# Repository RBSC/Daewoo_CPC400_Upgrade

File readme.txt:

-------------------------------------------------
Daewoo CPC-400/400S MSX2/MSX2+ Conversion Project
Created and Published by RBSC in 2026
Special thanks to Max Vlasov [Meteor-M]
-------------------------------------------------

The documentation for the project can be found in the DOCs folder of this repository. It consists of two PDF files. One file contains
information about the history of the project and how it was created, the second file contains instructions on how to make necessary
modifications to the hardware and what files to burn/flash into EPROM/GAL chips.

DISCLAIMER
----------

THIS INFORMATION AND RELATED FILES ARE PROVIDED AS IS AND ANY EXPRESS OR IMPLIED WARRANTIES, INCLUDING,BUT NOT LIMITED TO, THE IMPLIED
WARRANTIES OF MERCHANTABILITY AND FITNESS FOR A PARTICULAR PURPOSE ARE DISCLAIMED. IN NO EVENT SHALL THE COPYRIGHT OWNER OR CONTRIBUTORS
BE LIABLE FOR ANY DIRECT, INDIRECT, INCIDENTAL, SPECIAL, EXEMPLARY, OR CONSEQUENTIAL DAMAGES (INCLUDING, BUT NOT LIMITED TO, PROCUREMENT
OF SUBSTITUTE GOODS OR SERVICES; LOSS OF USE, DATA, OR PROFITS; OR BUSINESS INTERRUPTION) HOWEVER CAUSED AND ON ANY THEORY OF LIABILITY,
WHETHER IN CONTRACT, STRICT LIABILITY, OR TORT (INCLUDING NEGLIGENCE OR OTHERWISE) ARISING IN ANY WAY OUT OF THE USE OF THIS SOFTWARE,
EVEN IF ADVISED OF THE POSSIBILITY OF SUCH DAMAGE.

Contact information
-------------------

The members of RBSC group Tnt23, Wierzbowsky, Pyhesty, Ptero, GreyWolf, SuperMax, VWarlock, ALSP and DJS3000 can be contacted via the
group's e-mail address:
info@rbsc.su

The group's coordinator could be reached via this e-mail address:
admin@rbsc.su

The group's website can be found here:
https://rbsc.su/
https://rbsc.su/ru

The RBSC's hardware repository can be found here:
https://github.com/rbsc

The RBSC's 3D model repository can be found here:
https://www.thingiverse.com/groups/rbsc/things

-= ! MSX FOREVER ! =-

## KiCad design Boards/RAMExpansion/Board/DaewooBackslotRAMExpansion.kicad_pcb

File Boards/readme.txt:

-------------------------------------------------
Daewoo CPC-400/400S MSX2/MSX2+ Conversion Project
Created and Published by RBSC in 2026
Special thanks to Max Vlasov [Meteor-M]
-------------------------------------------------

These folders contain Gerber files, KiCAD source files. ROMs, BOMs, 3D case files and firmwares for the following boards:

FMPAC Light board (with stereo output)
Slot Expander Board
EPROM/SLOT Daughterboard
RAM Expansion Board
Older RAM Expansion Board (!different firmware for the Slot Expander is required!)

The boards and firmwares were created by Wierzbowsky [RBSC] and Max Vlasov [Meteor-M].

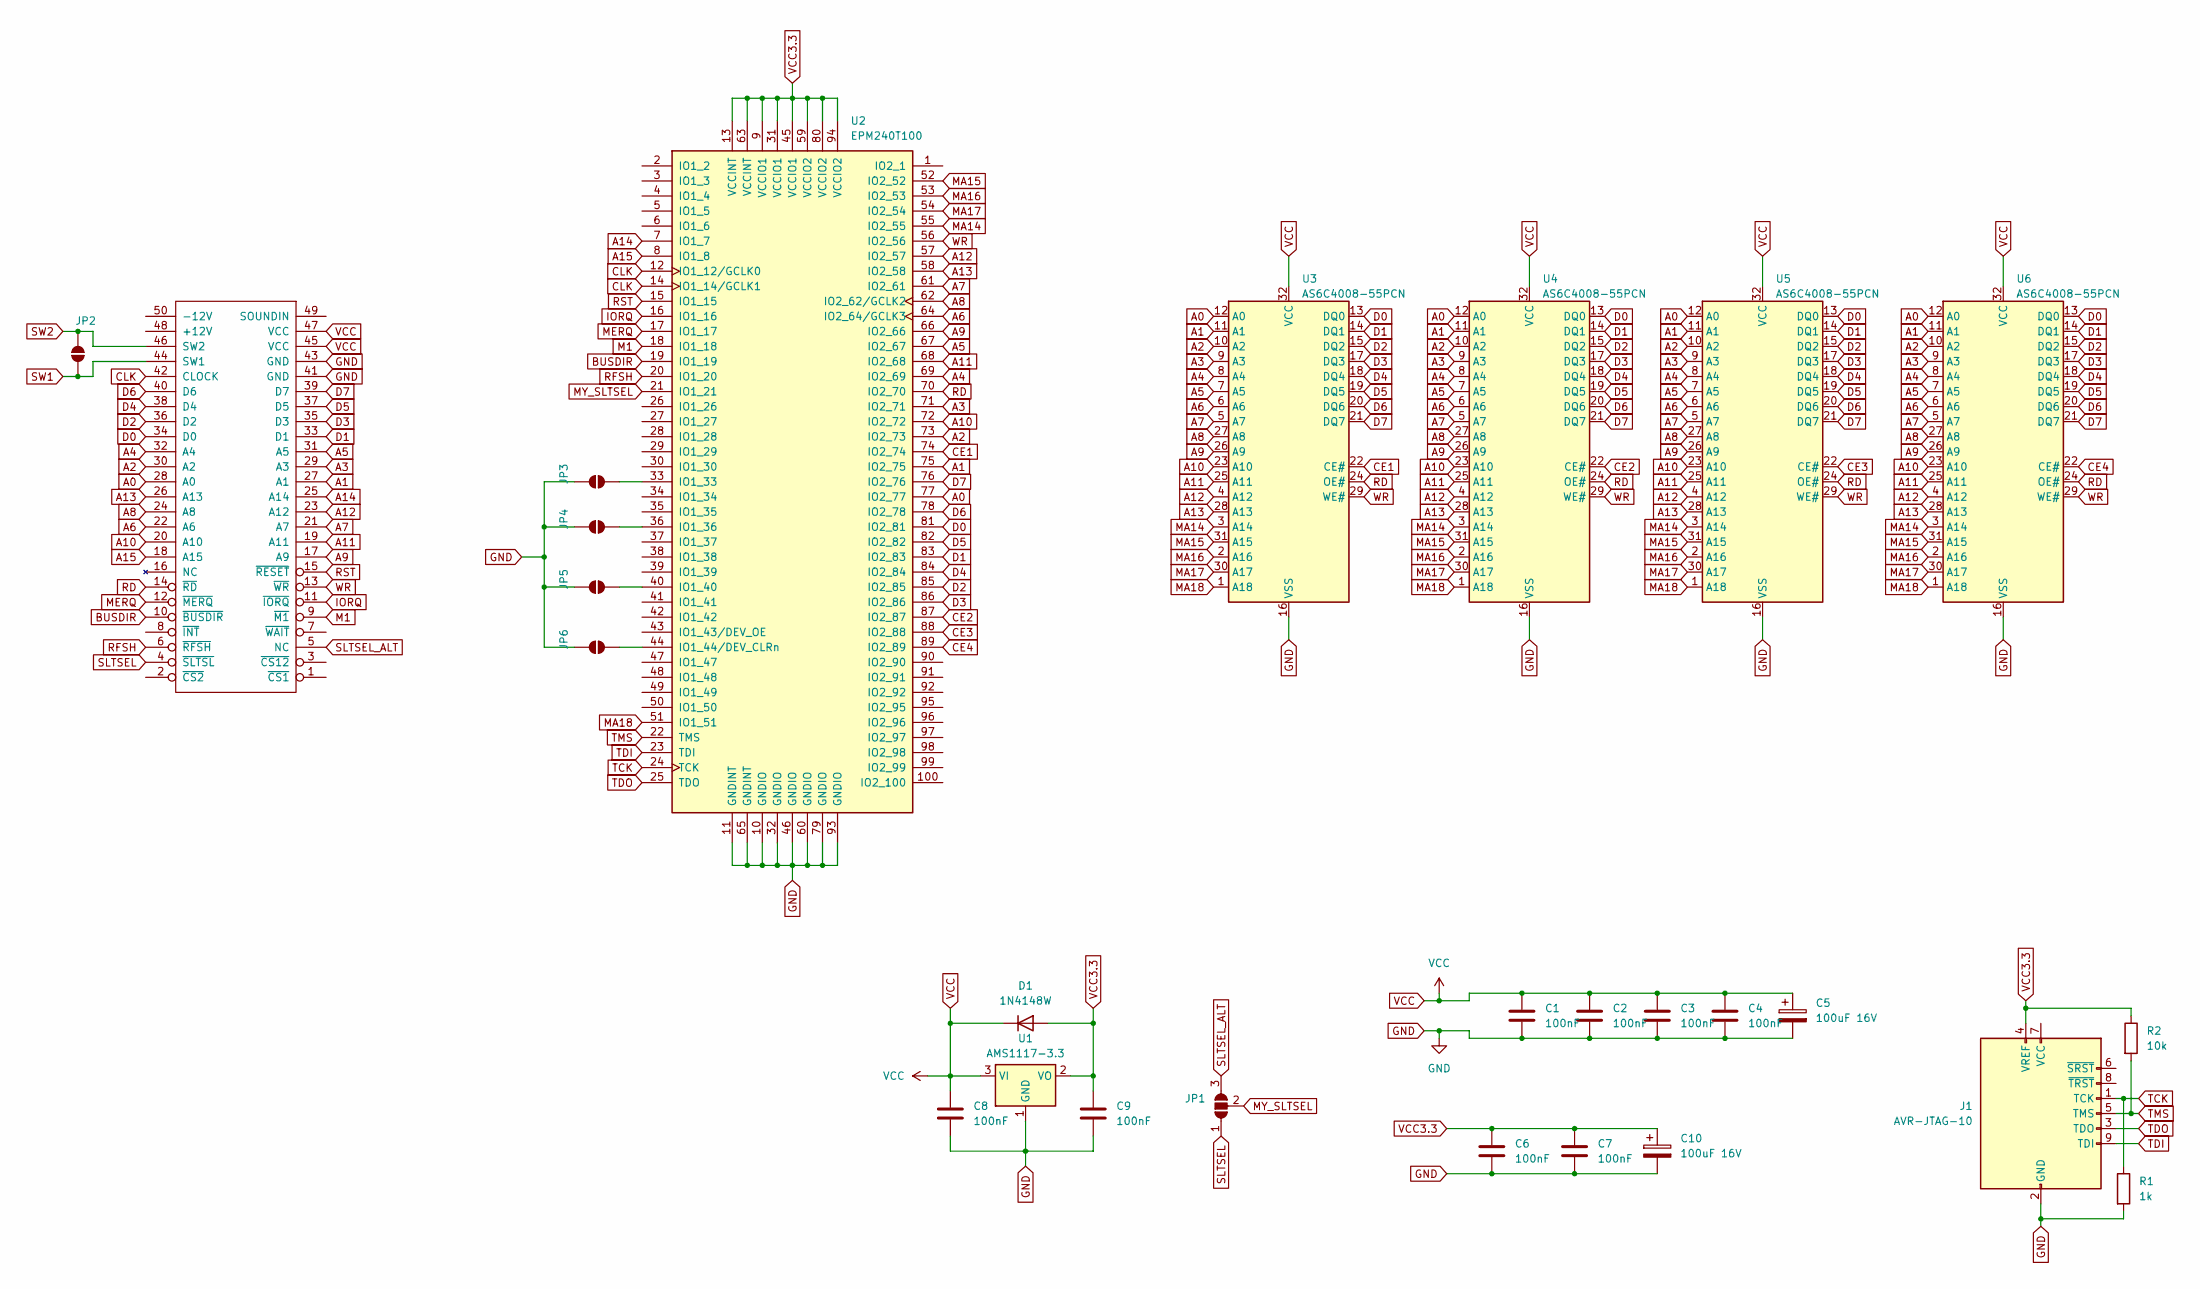
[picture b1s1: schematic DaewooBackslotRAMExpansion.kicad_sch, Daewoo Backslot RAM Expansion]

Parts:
BUS1: my_components_MSX_SLOT_HOST; DaewooBackSlotConnector
C1, C2, C3, C4, C6, C7, C8, C9: 100nF; C_0805_2012Metric
C5, C10: 100uF 16V; CP_Radial_D5.0mm_P2.00mm
D1: 1N4148W; D_SOD-123
J1: AVR-JTAG-10; IDC-Header_2x05_P2.54mm_Vertical
JP1: SolderJumper_3_Open; SolderJumper-3_P1.3mm_Open_RoundedPad1.0x1.5mm_NumberLabels
JP2, JP3, JP4, JP5, JP6: SolderJumper_2_Open; SolderJumper-2_P1.3mm_Open_RoundedPad1.0x1.5mm
R1: 1k; R_0805_2012Metric
R2: 10k; R_0805_2012Metric
U1: AMS1117-3.3; SOT-223-3_TabPin2
U2: EPM240T100; LQFP-100_14x14mm_P0.5mm
U3, U4, U5, U6: AS6C4008-55PCN; SOP-32_11.305x20.495mm_P1.27mm

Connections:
A0: BUS1.28 (A0), U2.77 (IO2_77), U3.12 (A0), U4.12 (A0), U5.12 (A0), U6.12 (A0)
A1: BUS1.27 (A1), U2.75 (IO2_75), U3.11 (A1), U4.11 (A1), U5.11 (A1), U6.11 (A1)
A2: BUS1.30 (A2), U2.73 (IO2_73), U3.10 (A2), U4.10 (A2), U5.10 (A2), U6.10 (A2)
A3: BUS1.29 (A3), U2.71 (IO2_71), U3.9 (A3), U4.9 (A3), U5.9 (A3), U6.9 (A3)
A4: BUS1.32 (A4), U2.69 (IO2_69), U3.8 (A4), U4.8 (A4), U5.8 (A4), U6.8 (A4)
A5: BUS1.31 (A5), U2.67 (IO2_67), U3.7 (A5), U4.7 (A5), U5.7 (A5), U6.7 (A5)
A6: BUS1.22 (A6), U2.64 (IO2_64/GCLK3), U3.6 (A6), U4.6 (A6), U5.6 (A6), U6.6 (A6)
A7: BUS1.21 (A7), U2.61 (IO2_61), U3.5 (A7), U4.5 (A7), U5.5 (A7), U6.5 (A7)
A8: BUS1.24 (A8), U2.62 (IO2_62/GCLK2), U3.27 (A8), U4.27 (A8), U5.27 (A8), U6.27 (A8)
A9: BUS1.17 (A9), U2.66 (IO2_66), U3.26 (A9), U4.26 (A9), U5.26 (A9), U6.26 (A9)
A10: BUS1.20 (A10), U2.72 (IO2_72), U3.23 (A10), U4.23 (A10), U5.23 (A10), U6.23 (A10)
A11: BUS1.19 (A11), U2.68 (IO2_68), U3.25 (A11), U4.25 (A11), U5.25 (A11), U6.25 (A11)
A12: BUS1.23 (A12), U2.57 (IO2_57), U3.4 (A12), U4.4 (A12), U5.4 (A12), U6.4 (A12)
A13: BUS1.26 (A13), U2.58 (IO2_58), U3.28 (A13), U4.28 (A13), U5.28 (A13), U6.28 (A13)
A14: BUS1.25 (A14), U2.7 (IO1_7)
A15: BUS1.18 (A15), U2.8 (IO1_8)
BUSDIR: BUS1.10 (~BUSDIR), U2.19 (IO1_19)
CE1: U2.74 (IO2_74), U3.22 (CE#)
CE2: U2.87 (IO2_87), U4.22 (CE#)
CE3: U2.88 (IO2_88), U5.22 (CE#)
CE4: U2.89 (IO2_89), U6.22 (CE#)
CLK: BUS1.42 (CLOCK), U2.12 (IO1_12/GCLK0), U2.14 (IO1_14/GCLK1)
D0: BUS1.34 (D0), U2.81 (IO2_81), U3.13 (DQ0), U4.13 (DQ0), U5.13 (DQ0), U6.13 (DQ0)
D1: BUS1.33 (D1), U2.83 (IO2_83), U3.14 (DQ1), U4.14 (DQ1), U5.14 (DQ1), U6.14 (DQ1)
D2: BUS1.36 (D2~), U2.85 (IO2_85), U3.15 (DQ2), U4.15 (DQ2), U5.15 (DQ2), U6.15 (DQ2)
D3: BUS1.35 (D3), U2.86 (IO2_86), U3.17 (DQ3), U4.17 (DQ3), U5.17 (DQ3), U6.17 (DQ3)
D4: BUS1.38 (D4), U2.84 (IO2_84), U3.18 (DQ4), U4.18 (DQ4), U5.18 (DQ4), U6.18 (DQ4)
D5: BUS1.37 (D5), U2.82 (IO2_82), U3.19 (DQ5), U4.19 (DQ5), U5.19 (DQ5), U6.19 (DQ5)
D6: BUS1.40 (D6), U2.78 (IO2_78), U3.20 (DQ6), U4.20 (DQ6), U5.20 (DQ6), U6.20 (DQ6)
D7: BUS1.39 (D7), U2.76 (IO2_76), U3.21 (DQ7), U4.21 (DQ7), U5.21 (DQ7), U6.21 (DQ7)
GND: BUS1.41 (GND), BUS1.43 (GND), C1.2, C2.2, C3.2, C4.2, C5.2, C6.2, C7.2, C8.2, C9.2, C10.2, J1.2 (GND), J1.10 (GND), JP3.2 (B), JP4.2 (B), JP5.2 (B), JP6.2 (B), R1.2, U1.1 (GND), U2.10 (GNDIO), U2.11 (GNDINT), U2.32 (GNDIO), U2.46 (GNDIO), U2.60 (GNDIO), U2.65 (GNDINT), U2.79 (GNDIO), U2.93 (GNDIO), U3.16 (VSS), U4.16 (VSS), U5.16 (VSS), U6.16 (VSS)
IORQ: BUS1.11 (~IORQ), U2.16 (IO1_16)
M1: BUS1.9 (~M1), U2.18 (IO1_18)
MA14: U2.55 (IO2_55), U3.3 (A14), U4.3 (A14), U5.3 (A14), U6.3 (A14)
MA15: U2.52 (IO2_52), U3.31 (A15), U4.31 (A15), U5.31 (A15), U6.31 (A15)
MA16: U2.53 (IO2_53), U3.2 (A16), U4.2 (A16), U5.2 (A16), U6.2 (A16)
MA17: U2.54 (IO2_54), U3.30 (A17), U4.30 (A17), U5.30 (A17), U6.30 (A17)
MA18: U2.51 (IO1_51), U3.1 (A18), U4.1 (A18), U5.1 (A18), U6.1 (A18)
MERQ: BUS1.12 (~MERQ), U2.17 (IO1_17)
MY_SLTSEL: JP1.2 (C), U2.21 (IO1_21)
unnamed: JP3.1 (A), U2.33 (IO1_33)
unnamed: JP4.1 (A), U2.36 (IO1_36)
unnamed: JP5.1 (A), U2.40 (IO1_40)
unnamed: JP6.1 (A), U2.44 (IO1_44/DEV_CLRn)
RD: BUS1.14 (~RD), U2.70 (IO2_70), U3.24 (OE#), U4.24 (OE#), U5.24 (OE#), U6.24 (OE#)
RFSH: BUS1.6 (~RFSH), U2.20 (IO1_20)
RST: BUS1.15 (~RESET), U2.15 (IO1_15)
SLTSEL: BUS1.4 (~SLTSL), JP1.1 (A)
SLTSEL_ALT: BUS1.5 (NC), JP1.3 (B)
SW1: BUS1.44 (SW1), JP2.1 (A)
SW2: BUS1.46 (SW2), JP2.2 (B)
TCK: J1.1 (TCK), R1.1, U2.24 (TCK)
TDI: J1.9 (TDI), U2.23 (TDI)
TDO: J1.3 (TDO), U2.25 (TDO)
TMS: J1.5 (TMS), R2.2, U2.22 (TMS)
VCC: BUS1.45 (VCC), BUS1.47 (VCC), C1.1, C2.1, C3.1, C4.1, C5.1, C8.1, D1.1 (K), U1.3 (VI), U3.32 (VCC), U4.32 (VCC), U5.32 (VCC), U6.32 (VCC)
VCC3.3: C6.1, C7.1, C9.1, C10.1, D1.2 (A), J1.4 (VREF), R2.1, U1.2 (VO), U2.9 (VCCIO1), U2.13 (VCCINT), U2.31 (VCCIO1), U2.45 (VCCIO1), U2.59 (VCCIO2), U2.63 (VCCINT), U2.80 (VCCIO2), U2.94 (VCCIO2)
WR: BUS1.13 (~WR), U2.56 (IO2_56), U3.29 (WE#), U4.29 (WE#), U5.29 (WE#), U6.29 (WE#)

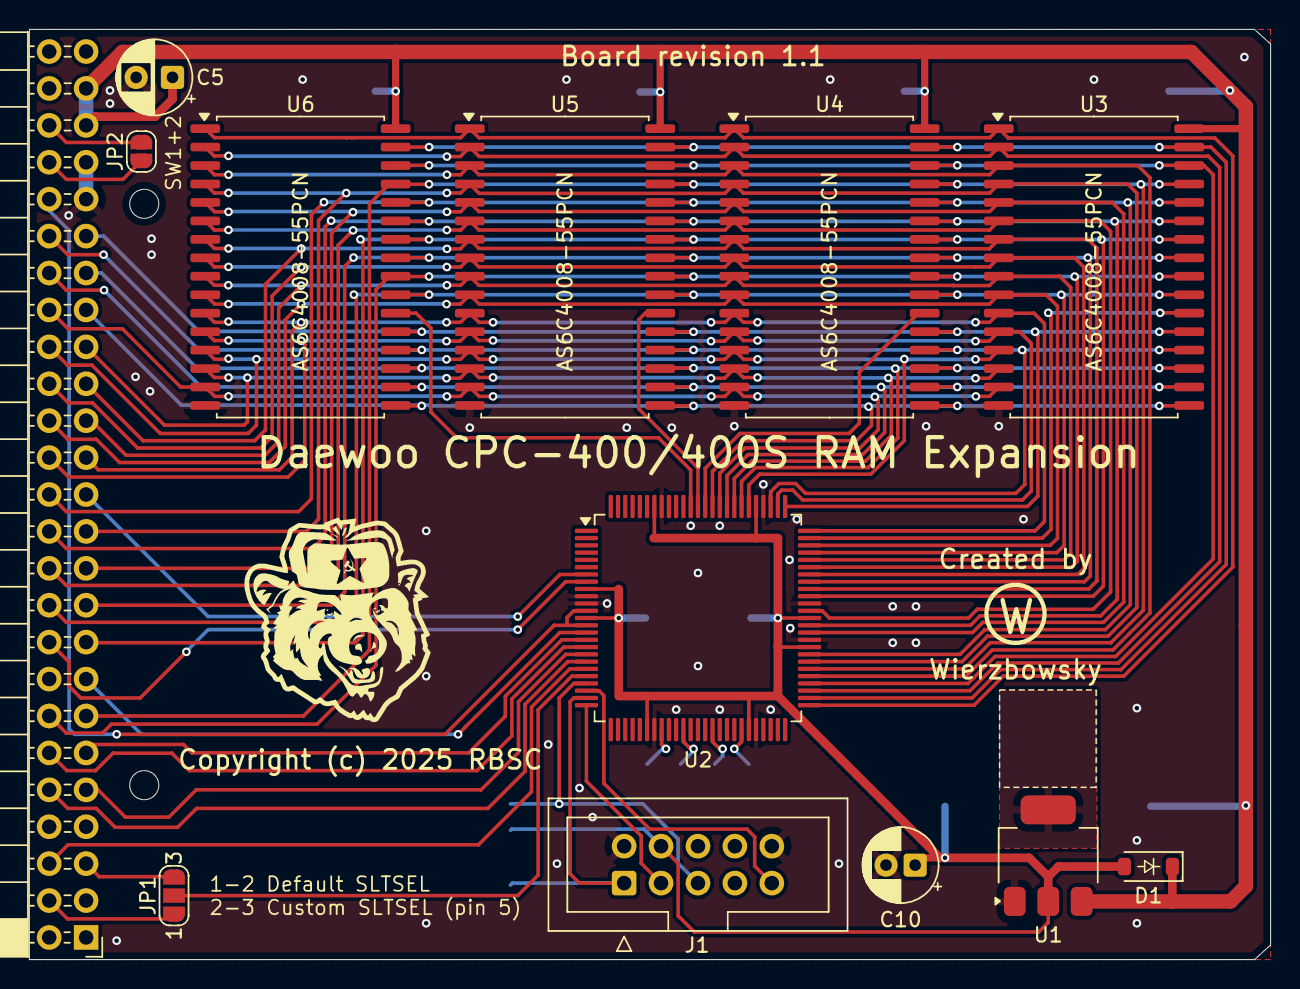
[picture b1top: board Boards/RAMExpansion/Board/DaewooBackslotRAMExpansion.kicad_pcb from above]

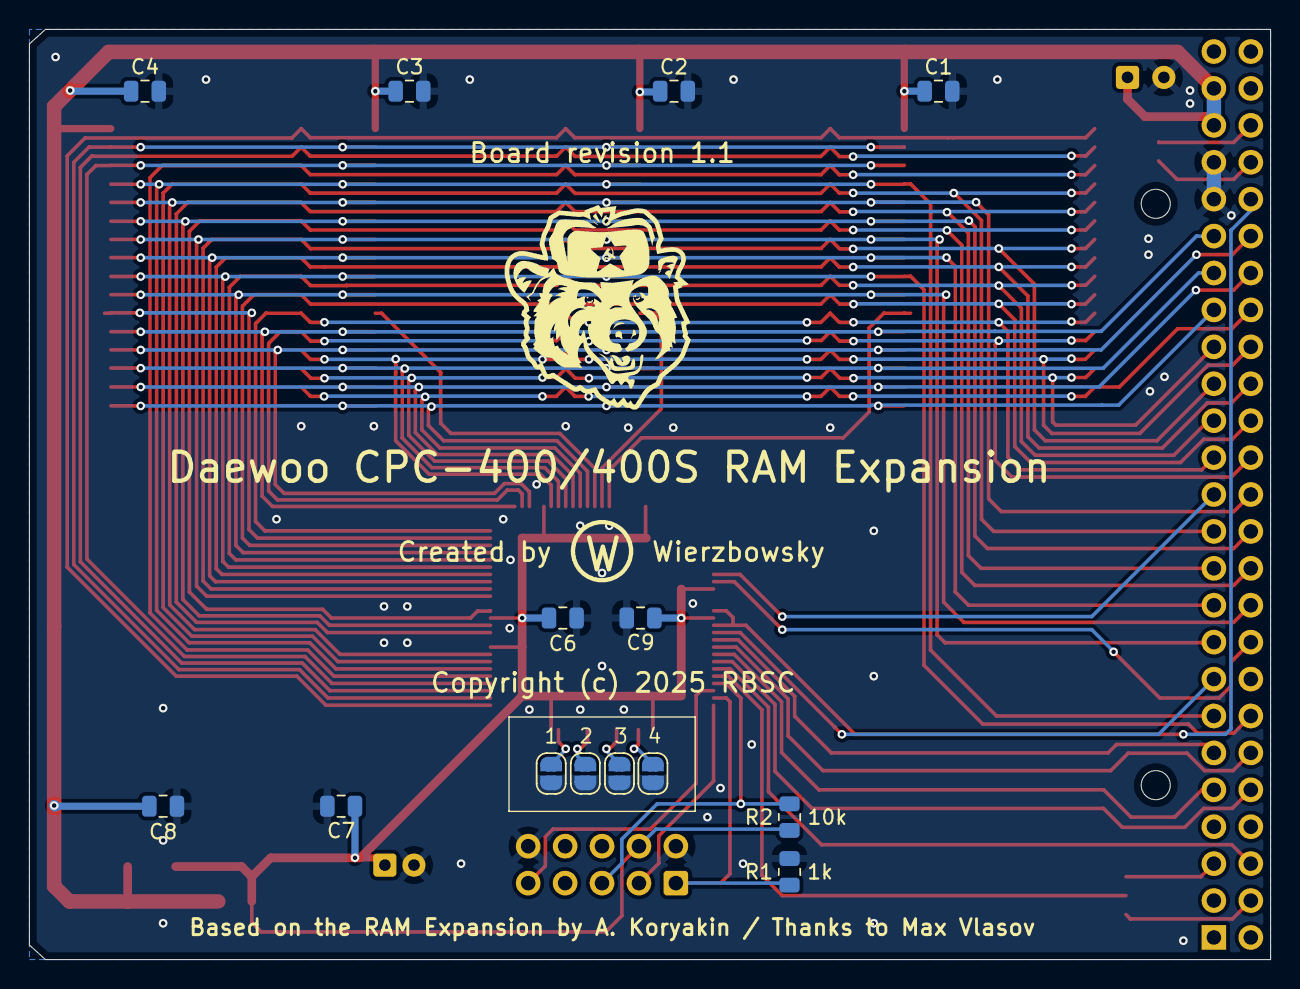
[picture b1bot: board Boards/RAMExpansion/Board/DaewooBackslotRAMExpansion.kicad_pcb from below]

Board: 2 copper layers, 85.4 x 64.0 mm, 27 parts (14 on the bottom side), 58 nets.

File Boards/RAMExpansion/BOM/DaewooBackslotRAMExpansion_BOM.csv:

"Id";"Designator";"Footprint";"Quantity";"Designation";"Supplier and ref";
1;"C5";"CP_Radial_D5.0mm_P2.50mm";1;"100uF 16V";;;
2;"D1";"D_SOD-123";1;"1N4148W";;;
3;"U5,U4,U3,U6";"SOP-32_11.305x20.495mm_P1.27mm";4;"AS6C4008-55PCN";;;
4;"U2";"LQFP-100_14x14mm_P0.5mm";1;"EPM240T100";;;
5;"U1";"SOT-223-3_TabPin2";1;"AMS1117-3.3";;;
6;"C10";"CP_Radial_D5.0mm_P2.00mm";1;"100uF 16V";;;
7;"J1";"IDC-Header_2x05_P2.54mm_Vertical";1;"AVR-JTAG-10";;;
8;"BUS1";"DaewooBackSlotConnector";1;"my_components_MSX_SLOT_HOST";;;
9;"C7,C2,C8,C4,C9,C3,C1,C6";"C_0805_2012Metric";8;"100nF";;;
10;"R2";"R_0805_2012Metric";1;"10k";;;
11;"R1";"R_0805_2012Metric";1;"1k";;;

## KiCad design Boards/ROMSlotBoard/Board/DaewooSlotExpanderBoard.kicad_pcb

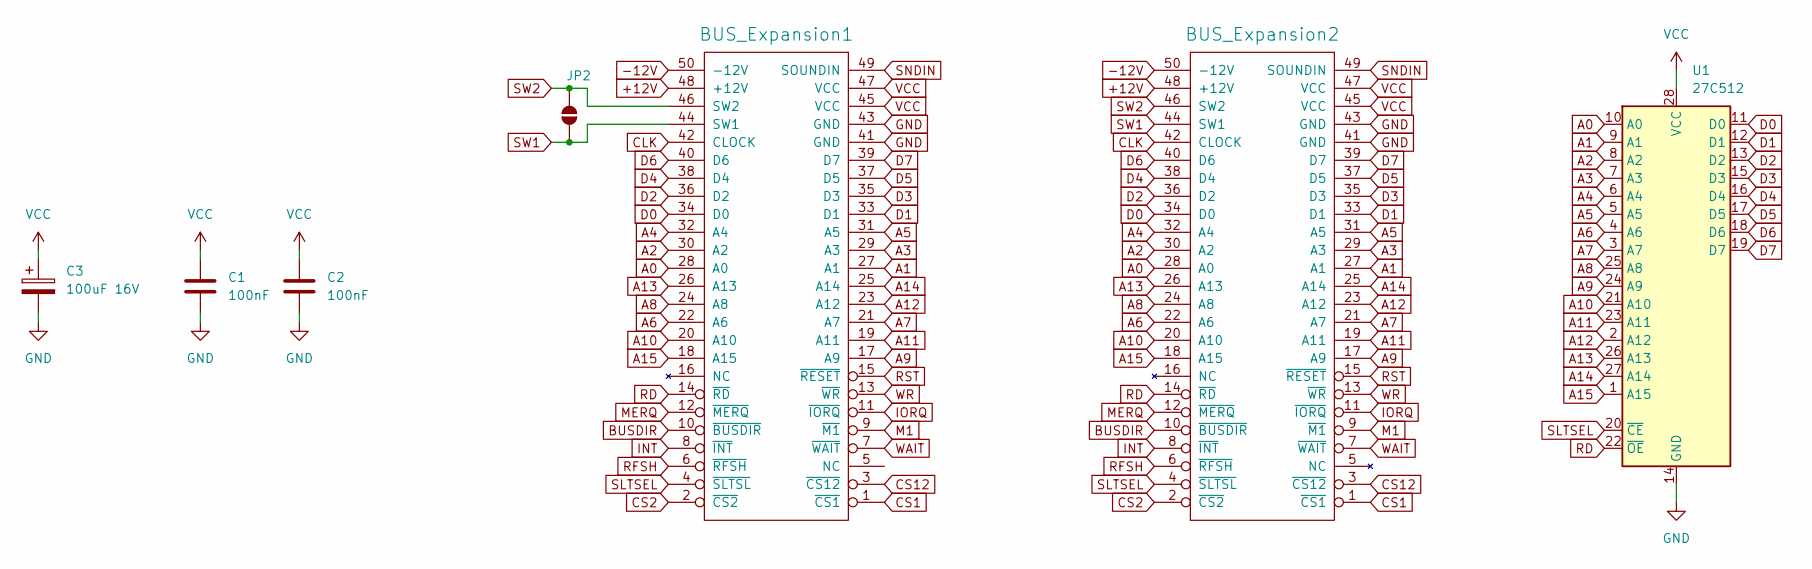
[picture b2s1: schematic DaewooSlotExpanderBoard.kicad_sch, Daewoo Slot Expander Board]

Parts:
BUS_Expansion1: my_components_MSX_SLOT_HOST; DaewooBackSlotConnector
BUS_Expansion2: my_components_MSX_SLOT_HOST; PinHeader_2x25_P2.54mm_Vertical
C1, C2: 100nF; C_0805_2012Metric
C3: 100uF 16V; CP_Radial_D5.0mm_P2.00mm
JP2: SolderJumper_2_Open; SolderJumper-2_P1.3mm_Open_RoundedPad1.0x1.5mm
U1: 27C512; DIP-28_W15.24mm

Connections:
+12V: BUS_Expansion1.48 (+12V), BUS_Expansion2.48 (+12V)
-12V: BUS_Expansion1.50 (-12V), BUS_Expansion2.50 (-12V)
A0: BUS_Expansion1.28 (A0), BUS_Expansion2.28 (A0), U1.10 (A0)
A1: BUS_Expansion1.27 (A1), BUS_Expansion2.27 (A1), U1.9 (A1)
A2: BUS_Expansion1.30 (A2), BUS_Expansion2.30 (A2), U1.8 (A2)
A3: BUS_Expansion1.29 (A3), BUS_Expansion2.29 (A3), U1.7 (A3)
A4: BUS_Expansion1.32 (A4), BUS_Expansion2.32 (A4), U1.6 (A4)
A5: BUS_Expansion1.31 (A5), BUS_Expansion2.31 (A5), U1.5 (A5)
A6: BUS_Expansion1.22 (A6), BUS_Expansion2.22 (A6), U1.4 (A6)
A7: BUS_Expansion1.21 (A7), BUS_Expansion2.21 (A7), U1.3 (A7)
A8: BUS_Expansion1.24 (A8), BUS_Expansion2.24 (A8), U1.25 (A8)
A9: BUS_Expansion1.17 (A9), BUS_Expansion2.17 (A9), U1.24 (A9)
A10: BUS_Expansion1.20 (A10), BUS_Expansion2.20 (A10), U1.21 (A10)
A11: BUS_Expansion1.19 (A11), BUS_Expansion2.19 (A11), U1.23 (A11)
A12: BUS_Expansion1.23 (A12), BUS_Expansion2.23 (A12), U1.2 (A12)
A13: BUS_Expansion1.26 (A13), BUS_Expansion2.26 (A13), U1.26 (A13)
A14: BUS_Expansion1.25 (A14), BUS_Expansion2.25 (A14), U1.27 (A14)
A15: BUS_Expansion1.18 (A15), BUS_Expansion2.18 (A15), U1.1 (A15)
BUSDIR: BUS_Expansion1.10 (~BUSDIR), BUS_Expansion2.10 (~BUSDIR)
CLK: BUS_Expansion1.42 (CLOCK), BUS_Expansion2.42 (CLOCK)
CS1: BUS_Expansion1.1 (~CS1), BUS_Expansion2.1 (~CS1)
CS2: BUS_Expansion1.2 (~CS2), BUS_Expansion2.2 (~CS2)
CS12: BUS_Expansion1.3 (~CS12), BUS_Expansion2.3 (~CS12)
D0: BUS_Expansion1.34 (D0), BUS_Expansion2.34 (D0), U1.11 (D0)
D1: BUS_Expansion1.33 (D1), BUS_Expansion2.33 (D1), U1.12 (D1)
D2: BUS_Expansion1.36 (D2~), BUS_Expansion2.36 (D2~), U1.13 (D2)
D3: BUS_Expansion1.35 (D3), BUS_Expansion2.35 (D3), U1.15 (D3)
D4: BUS_Expansion1.38 (D4), BUS_Expansion2.38 (D4), U1.16 (D4)
D5: BUS_Expansion1.37 (D5), BUS_Expansion2.37 (D5), U1.17 (D5)
D6: BUS_Expansion1.40 (D6), BUS_Expansion2.40 (D6), U1.18 (D6)
D7: BUS_Expansion1.39 (D7), BUS_Expansion2.39 (D7), U1.19 (D7)
GND: BUS_Expansion1.41 (GND), BUS_Expansion1.43 (GND), BUS_Expansion2.41 (GND), BUS_Expansion2.43 (GND), C1.2, C2.2, C3.2, U1.14 (GND)
INT: BUS_Expansion1.8 (~INT), BUS_Expansion2.8 (~INT)
IORQ: BUS_Expansion1.11 (~IORQ), BUS_Expansion2.11 (~IORQ)
M1: BUS_Expansion1.9 (~M1), BUS_Expansion2.9 (~M1)
MERQ: BUS_Expansion1.12 (~MERQ), BUS_Expansion2.12 (~MERQ)
RD: BUS_Expansion1.14 (~RD), BUS_Expansion2.14 (~RD), U1.22 (~OE)
RFSH: BUS_Expansion1.6 (~RFSH), BUS_Expansion2.6 (~RFSH)
RST: BUS_Expansion1.15 (~RESET), BUS_Expansion2.15 (~RESET)
SLTSEL: BUS_Expansion1.4 (~SLTSL), BUS_Expansion2.4 (~SLTSL), U1.20 (~CE)
SNDIN: BUS_Expansion1.49 (SOUNDIN), BUS_Expansion2.49 (SOUNDIN)
SW1: BUS_Expansion1.44 (SW1), BUS_Expansion2.44 (SW1), JP2.1 (A)
SW2: BUS_Expansion1.46 (SW2), BUS_Expansion2.46 (SW2), JP2.2 (B)
VCC: BUS_Expansion1.45 (VCC), BUS_Expansion1.47 (VCC), BUS_Expansion2.45 (VCC), BUS_Expansion2.47 (VCC), C1.1, C2.1, C3.1, U1.28 (VCC)
WAIT: BUS_Expansion1.7 (~WAIT), BUS_Expansion2.7 (~WAIT)
WR: BUS_Expansion1.13 (~WR), BUS_Expansion2.13 (~WR)

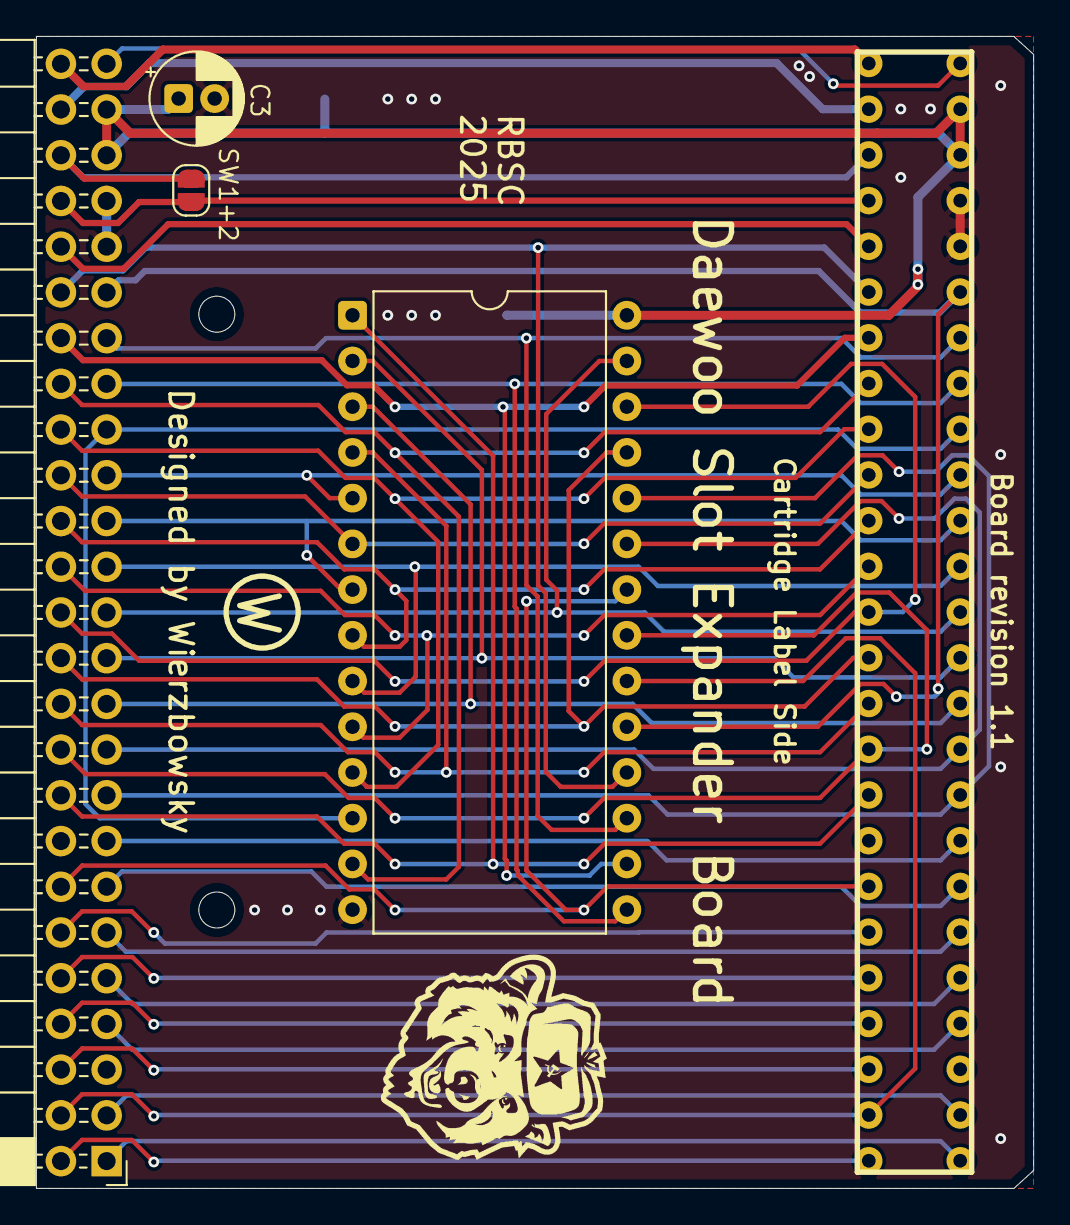
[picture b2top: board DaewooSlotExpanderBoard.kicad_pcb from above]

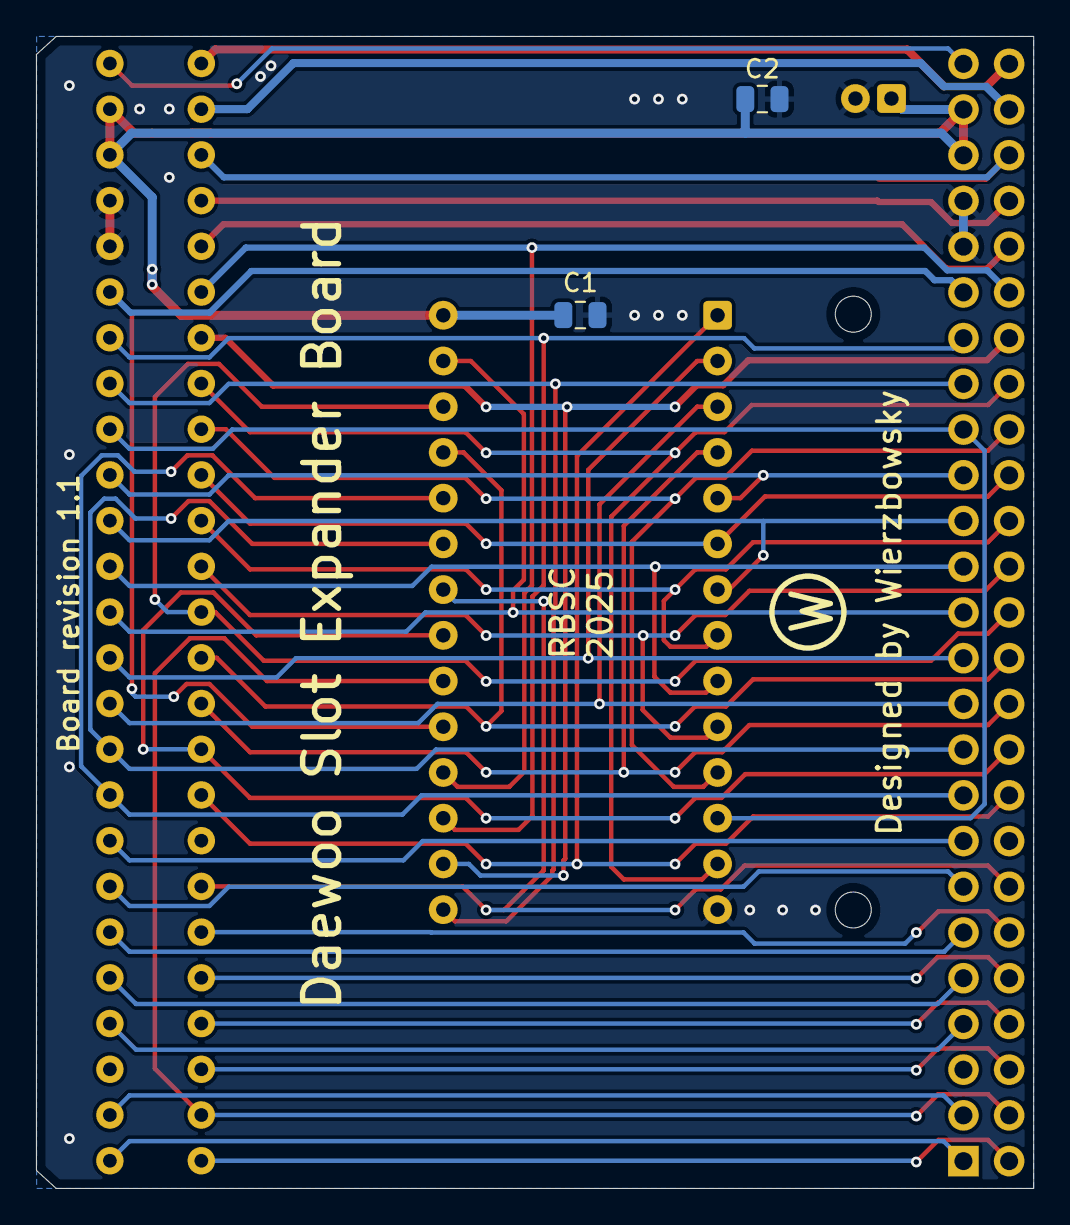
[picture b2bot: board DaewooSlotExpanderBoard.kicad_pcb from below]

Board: 2 copper layers, 55.4 x 64.0 mm, 7 parts (2 on the bottom side), 46 nets.

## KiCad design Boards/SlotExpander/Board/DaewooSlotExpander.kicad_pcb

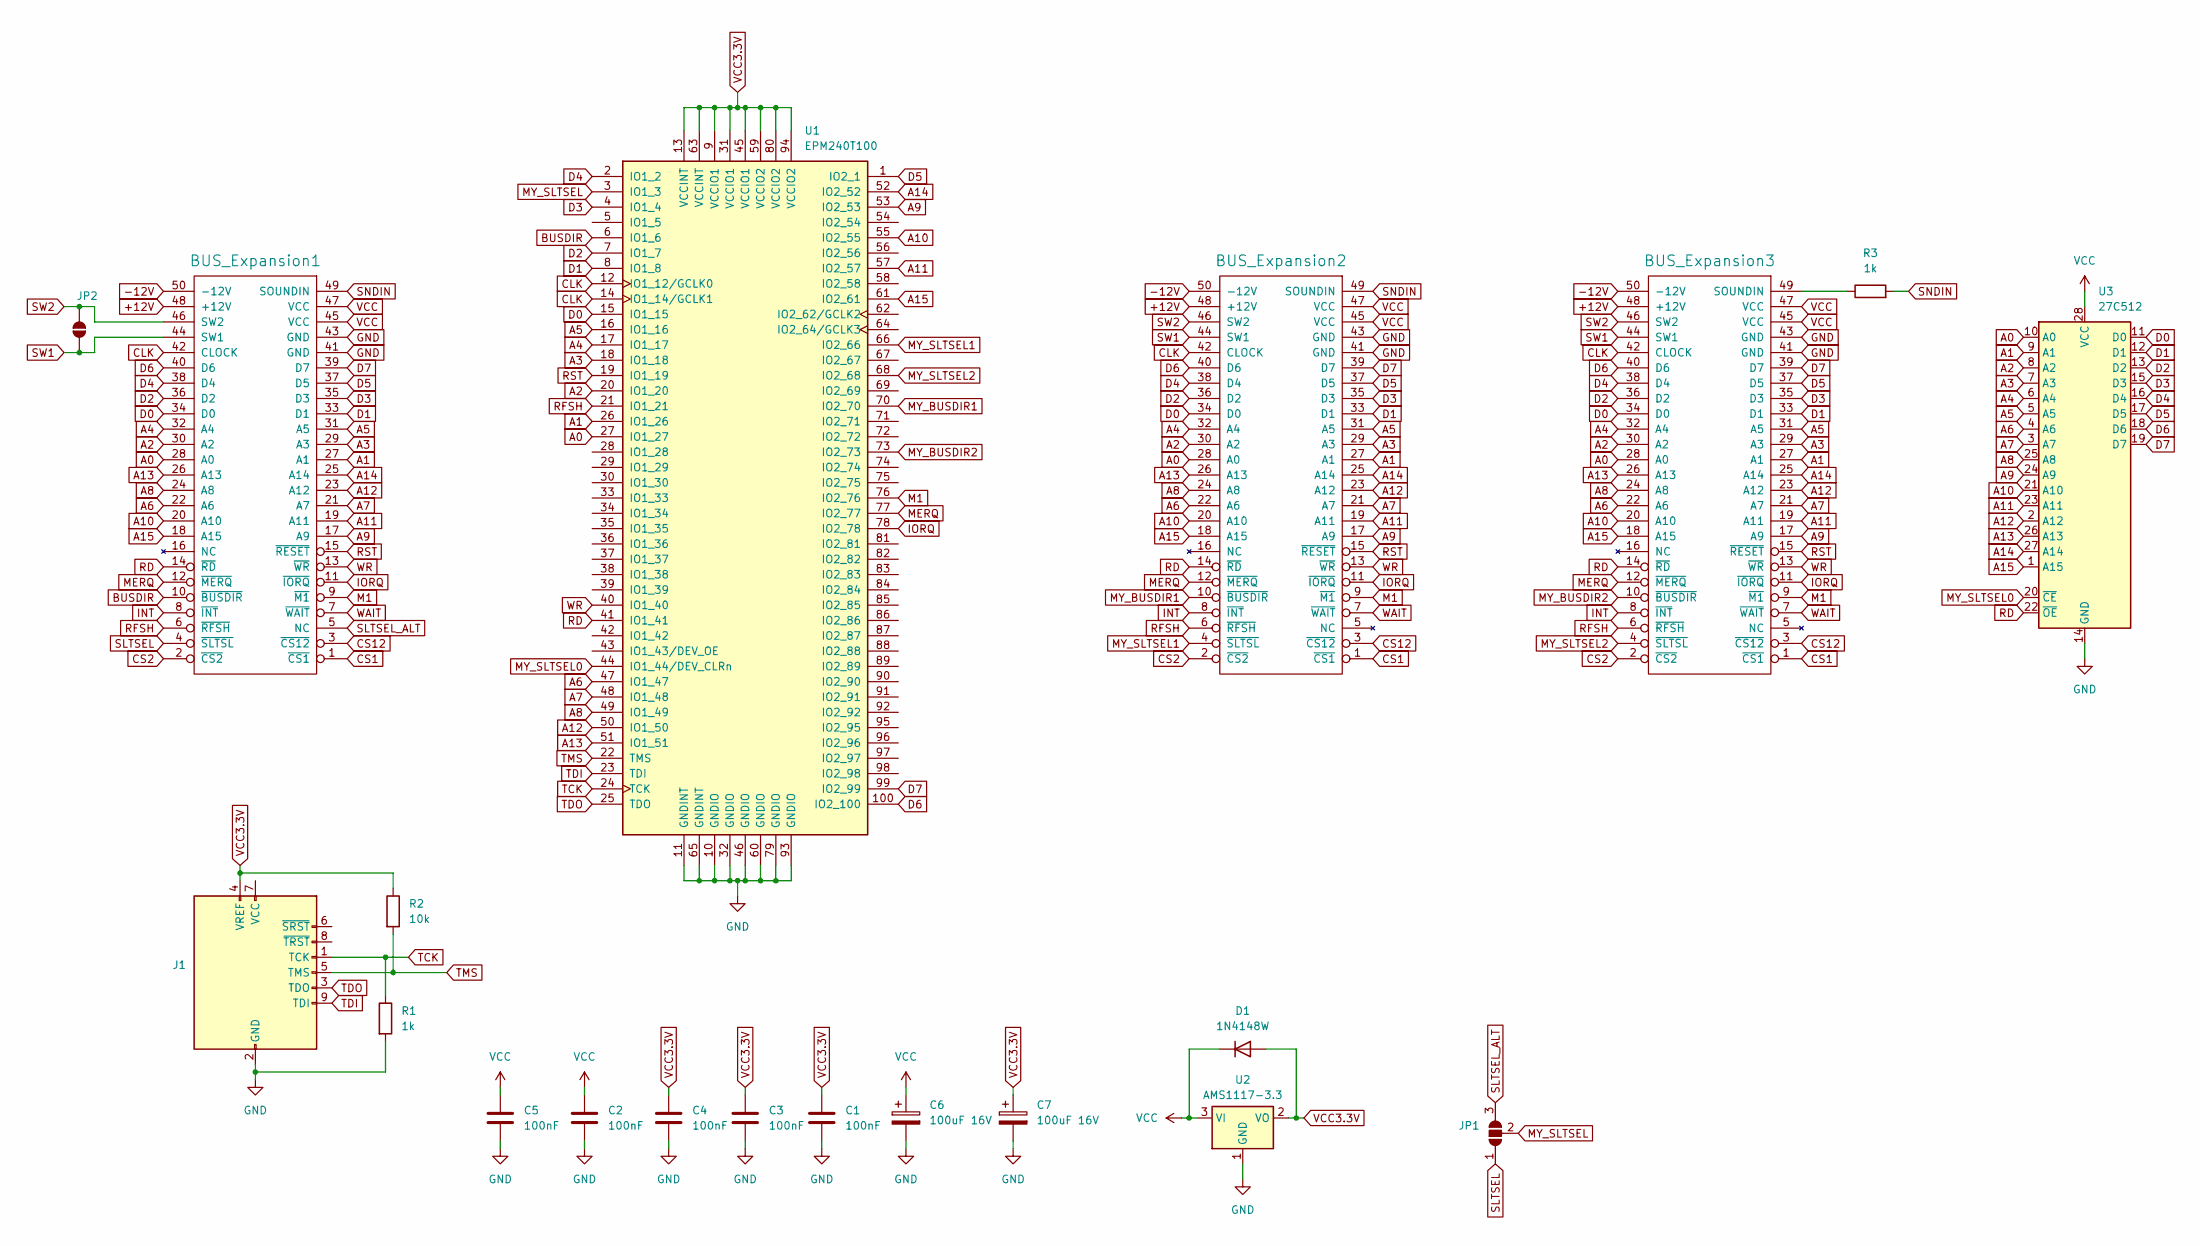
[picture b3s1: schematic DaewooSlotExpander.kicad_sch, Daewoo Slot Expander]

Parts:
BUS_Expansion1: my_components_MSX_SLOT_HOST; DaewooBackSlotConnector
BUS_Expansion2, BUS_Expansion3: my_components_MSX_SLOT_HOST; PinHeader_2x25_P2.54mm_Vertical
C1, C2, C3, C4, C5: 100nF; C_0805_2012Metric
C6, C7: 100uF 16V; CP_Radial_D5.0mm_P2.00mm
D1: 1N4148W; D_SOD-123
J1: AVR-JTAG-10; IDC-Header_2x05_P2.54mm_Vertical
JP1: SolderJumper_3_Open; SolderJumper-3_P1.3mm_Open_RoundedPad1.0x1.5mm_NumberLabels
JP2: SolderJumper_2_Open; SolderJumper-2_P1.3mm_Open_RoundedPad1.0x1.5mm
R1, R3: 1k; R_0805_2012Metric
R2: 10k; R_0805_2012Metric
U1: EPM240T100; LQFP-100_14x14mm_P0.5mm
U2: AMS1117-3.3; SOT-223-3_TabPin2
U3: 27C512; DIP-28_W15.24mm

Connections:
+12V: BUS_Expansion1.48 (+12V), BUS_Expansion2.48 (+12V), BUS_Expansion3.48 (+12V)
-12V: BUS_Expansion1.50 (-12V), BUS_Expansion2.50 (-12V), BUS_Expansion3.50 (-12V)
A0: BUS_Expansion1.28 (A0), BUS_Expansion2.28 (A0), BUS_Expansion3.28 (A0), U1.27 (IO1_27), U3.10 (A0)
A1: BUS_Expansion1.27 (A1), BUS_Expansion2.27 (A1), BUS_Expansion3.27 (A1), U1.26 (IO1_26), U3.9 (A1)
A2: BUS_Expansion1.30 (A2), BUS_Expansion2.30 (A2), BUS_Expansion3.30 (A2), U1.20 (IO1_20), U3.8 (A2)
A3: BUS_Expansion1.29 (A3), BUS_Expansion2.29 (A3), BUS_Expansion3.29 (A3), U1.18 (IO1_18), U3.7 (A3)
A4: BUS_Expansion1.32 (A4), BUS_Expansion2.32 (A4), BUS_Expansion3.32 (A4), U1.17 (IO1_17), U3.6 (A4)
A5: BUS_Expansion1.31 (A5), BUS_Expansion2.31 (A5), BUS_Expansion3.31 (A5), U1.16 (IO1_16), U3.5 (A5)
A6: BUS_Expansion1.22 (A6), BUS_Expansion2.22 (A6), BUS_Expansion3.22 (A6), U1.47 (IO1_47), U3.4 (A6)
A7: BUS_Expansion1.21 (A7), BUS_Expansion2.21 (A7), BUS_Expansion3.21 (A7), U1.48 (IO1_48), U3.3 (A7)
A8: BUS_Expansion1.24 (A8), BUS_Expansion2.24 (A8), BUS_Expansion3.24 (A8), U1.49 (IO1_49), U3.25 (A8)
A9: BUS_Expansion1.17 (A9), BUS_Expansion2.17 (A9), BUS_Expansion3.17 (A9), U1.53 (IO2_53), U3.24 (A9)
A10: BUS_Expansion1.20 (A10), BUS_Expansion2.20 (A10), BUS_Expansion3.20 (A10), U1.55 (IO2_55), U3.21 (A10)
A11: BUS_Expansion1.19 (A11), BUS_Expansion2.19 (A11), BUS_Expansion3.19 (A11), U1.57 (IO2_57), U3.23 (A11)
A12: BUS_Expansion1.23 (A12), BUS_Expansion2.23 (A12), BUS_Expansion3.23 (A12), U1.50 (IO1_50), U3.2 (A12)
A13: BUS_Expansion1.26 (A13), BUS_Expansion2.26 (A13), BUS_Expansion3.26 (A13), U1.51 (IO1_51), U3.26 (A13)
A14: BUS_Expansion1.25 (A14), BUS_Expansion2.25 (A14), BUS_Expansion3.25 (A14), U1.52 (IO2_52), U3.27 (A14)
A15: BUS_Expansion1.18 (A15), BUS_Expansion2.18 (A15), BUS_Expansion3.18 (A15), U1.61 (IO2_61), U3.1 (A15)
BUSDIR: BUS_Expansion1.10 (~BUSDIR), U1.6 (IO1_6)
CLK: BUS_Expansion1.42 (CLOCK), BUS_Expansion2.42 (CLOCK), BUS_Expansion3.42 (CLOCK), U1.12 (IO1_12/GCLK0), U1.14 (IO1_14/GCLK1)
CS1: BUS_Expansion1.1 (~CS1), BUS_Expansion2.1 (~CS1), BUS_Expansion3.1 (~CS1)
CS2: BUS_Expansion1.2 (~CS2), BUS_Expansion2.2 (~CS2), BUS_Expansion3.2 (~CS2)
CS12: BUS_Expansion1.3 (~CS12), BUS_Expansion2.3 (~CS12), BUS_Expansion3.3 (~CS12)
D0: BUS_Expansion1.34 (D0), BUS_Expansion2.34 (D0), BUS_Expansion3.34 (D0), U1.15 (IO1_15), U3.11 (D0)
D1: BUS_Expansion1.33 (D1), BUS_Expansion2.33 (D1), BUS_Expansion3.33 (D1), U1.8 (IO1_8), U3.12 (D1)
D2: BUS_Expansion1.36 (D2~), BUS_Expansion2.36 (D2~), BUS_Expansion3.36 (D2~), U1.7 (IO1_7), U3.13 (D2)
D3: BUS_Expansion1.35 (D3), BUS_Expansion2.35 (D3), BUS_Expansion3.35 (D3), U1.4 (IO1_4), U3.15 (D3)
D4: BUS_Expansion1.38 (D4), BUS_Expansion2.38 (D4), BUS_Expansion3.38 (D4), U1.2 (IO1_2), U3.16 (D4)
D5: BUS_Expansion1.37 (D5), BUS_Expansion2.37 (D5), BUS_Expansion3.37 (D5), U1.1 (IO2_1), U3.17 (D5)
D6: BUS_Expansion1.40 (D6), BUS_Expansion2.40 (D6), BUS_Expansion3.40 (D6), U1.100 (IO2_100), U3.18 (D6)
D7: BUS_Expansion1.39 (D7), BUS_Expansion2.39 (D7), BUS_Expansion3.39 (D7), U1.99 (IO2_99), U3.19 (D7)
GND: BUS_Expansion1.41 (GND), BUS_Expansion1.43 (GND), BUS_Expansion2.41 (GND), BUS_Expansion2.43 (GND), BUS_Expansion3.41 (GND), BUS_Expansion3.43 (GND), C1.2, C2.2, C3.2, C4.2, C5.2, C6.2, C7.2, J1.2 (GND), J1.10 (GND), R1.2, U1.10 (GNDIO), U1.11 (GNDINT), U1.32 (GNDIO), U1.46 (GNDIO), U1.60 (GNDIO), U1.65 (GNDINT), U1.79 (GNDIO), U1.93 (GNDIO), U2.1 (GND), U3.14 (GND)
INT: BUS_Expansion1.8 (~INT), BUS_Expansion2.8 (~INT), BUS_Expansion3.8 (~INT)
IORQ: BUS_Expansion1.11 (~IORQ), BUS_Expansion2.11 (~IORQ), BUS_Expansion3.11 (~IORQ), U1.78 (IO2_78)
M1: BUS_Expansion1.9 (~M1), BUS_Expansion2.9 (~M1), BUS_Expansion3.9 (~M1), U1.76 (IO2_76)
MERQ: BUS_Expansion1.12 (~MERQ), BUS_Expansion2.12 (~MERQ), BUS_Expansion3.12 (~MERQ), U1.77 (IO2_77)
MY_BUSDIR1: BUS_Expansion2.10 (~BUSDIR), U1.70 (IO2_70)
MY_BUSDIR2: BUS_Expansion3.10 (~BUSDIR), U1.73 (IO2_73)
MY_SLTSEL: JP1.2 (C), U1.3 (IO1_3)
MY_SLTSEL0: U1.44 (IO1_44/DEV_CLRn), U3.20 (~CE)
MY_SLTSEL1: BUS_Expansion2.4 (~SLTSL), U1.66 (IO2_66)
MY_SLTSEL2: BUS_Expansion3.4 (~SLTSL), U1.68 (IO2_68)
unnamed: BUS_Expansion3.49 (SOUNDIN), R3.1
RD: BUS_Expansion1.14 (~RD), BUS_Expansion2.14 (~RD), BUS_Expansion3.14 (~RD), U1.41 (IO1_41), U3.22 (~OE)
RFSH: BUS_Expansion1.6 (~RFSH), BUS_Expansion2.6 (~RFSH), BUS_Expansion3.6 (~RFSH), U1.21 (IO1_21)
RST: BUS_Expansion1.15 (~RESET), BUS_Expansion2.15 (~RESET), BUS_Expansion3.15 (~RESET), U1.19 (IO1_19)
SLTSEL: BUS_Expansion1.4 (~SLTSL), JP1.1 (A)
SLTSEL_ALT: BUS_Expansion1.5 (NC), JP1.3 (B)
SNDIN: BUS_Expansion1.49 (SOUNDIN), BUS_Expansion2.49 (SOUNDIN), R3.2
SW1: BUS_Expansion1.44 (SW1), BUS_Expansion2.44 (SW1), BUS_Expansion3.44 (SW1), JP2.1 (A)
SW2: BUS_Expansion1.46 (SW2), BUS_Expansion2.46 (SW2), BUS_Expansion3.46 (SW2), JP2.2 (B)
TCK: J1.1 (TCK), R1.1, U1.24 (TCK)
TDI: J1.9 (TDI), U1.23 (TDI)
TDO: J1.3 (TDO), U1.25 (TDO)
TMS: J1.5 (TMS), R2.2, U1.22 (TMS)
VCC: BUS_Expansion1.45 (VCC), BUS_Expansion1.47 (VCC), BUS_Expansion2.45 (VCC), BUS_Expansion2.47 (VCC), BUS_Expansion3.45 (VCC), BUS_Expansion3.47 (VCC), C2.1, C5.1, C6.1, D1.1 (K), U2.3 (VI), U3.28 (VCC)
VCC3.3V: C1.1, C3.1, C4.1, C7.1, D1.2 (A), J1.4 (VREF), R2.1, U1.9 (VCCIO1), U1.13 (VCCINT), U1.31 (VCCIO1), U1.45 (VCCIO1), U1.59 (VCCIO2), U1.63 (VCCINT), U1.80 (VCCIO2), U1.94 (VCCIO2), U2.2 (VO)
WAIT: BUS_Expansion1.7 (~WAIT), BUS_Expansion2.7 (~WAIT), BUS_Expansion3.7 (~WAIT)
WR: BUS_Expansion1.13 (~WR), BUS_Expansion2.13 (~WR), BUS_Expansion3.13 (~WR), U1.40 (IO1_40)

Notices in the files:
Boards/FMPAC/Board/DaewooBackslotFMPAC.kicad_pcb:
Copyright (c) 2025
(C) 2025 RBSC
Boards/RAMExpansion/Board/DaewooBackslotRAMExpansion.kicad_pcb:
Copyright (c) 2025 RBSC
